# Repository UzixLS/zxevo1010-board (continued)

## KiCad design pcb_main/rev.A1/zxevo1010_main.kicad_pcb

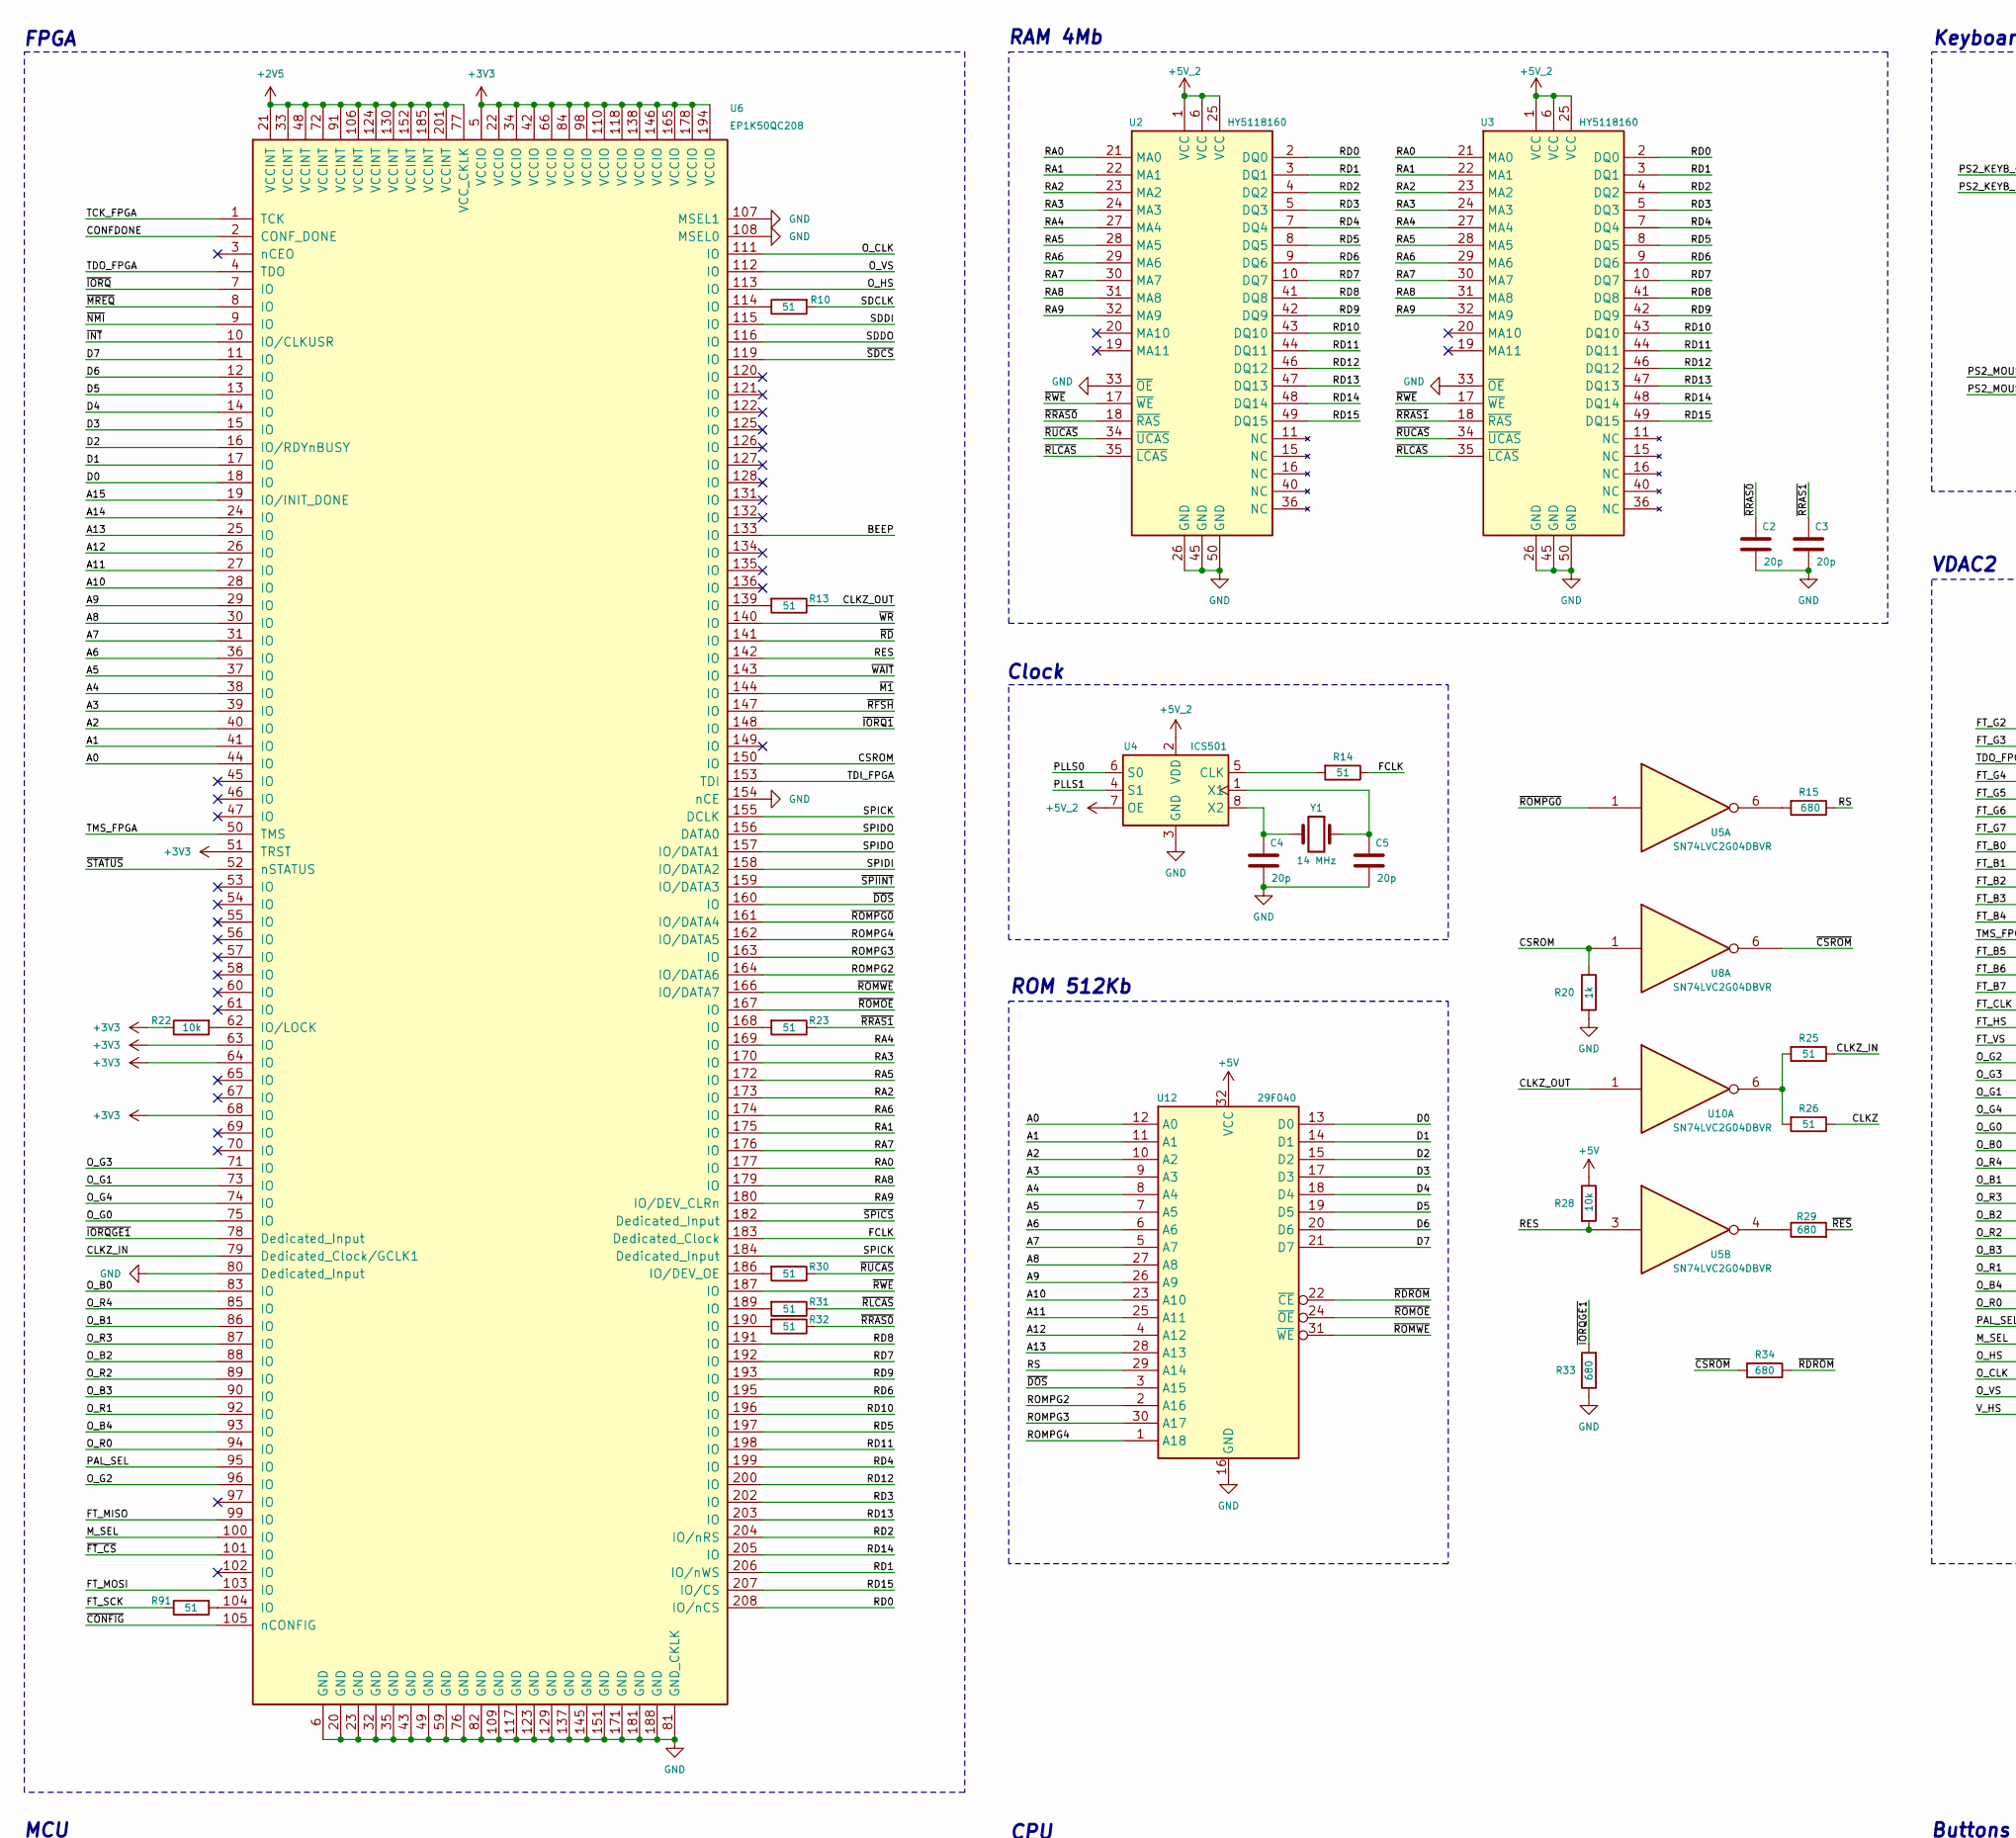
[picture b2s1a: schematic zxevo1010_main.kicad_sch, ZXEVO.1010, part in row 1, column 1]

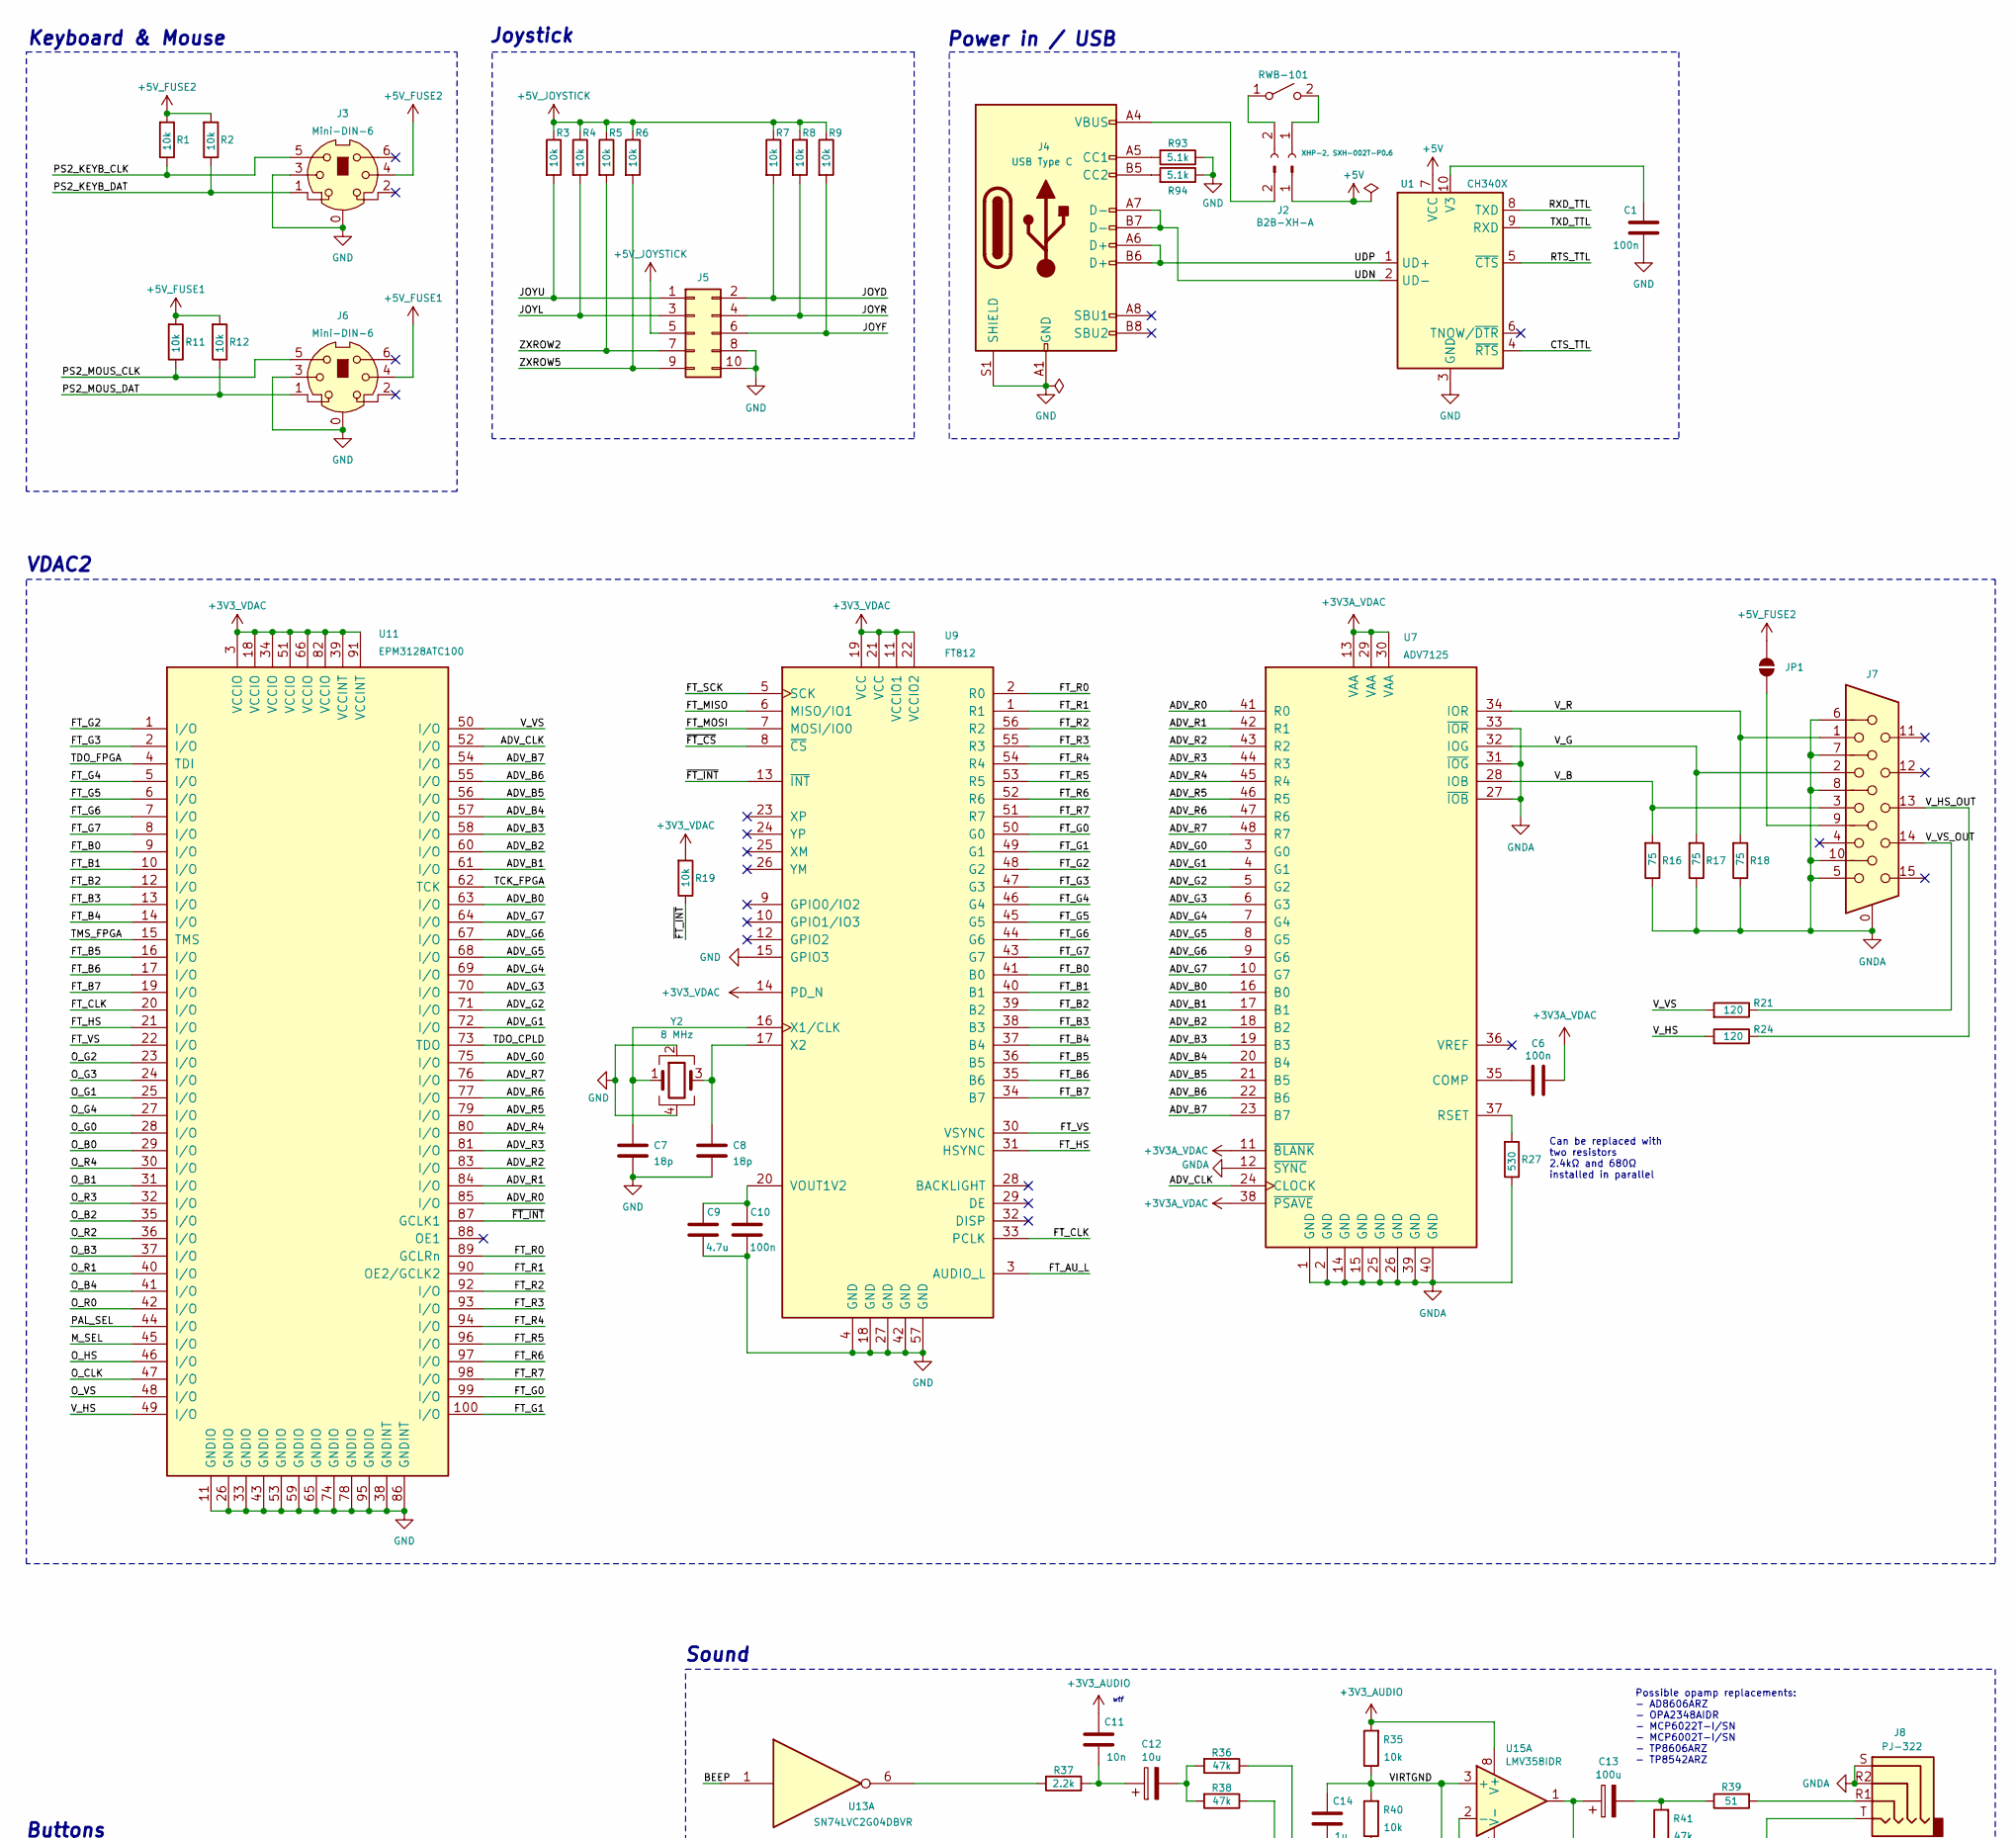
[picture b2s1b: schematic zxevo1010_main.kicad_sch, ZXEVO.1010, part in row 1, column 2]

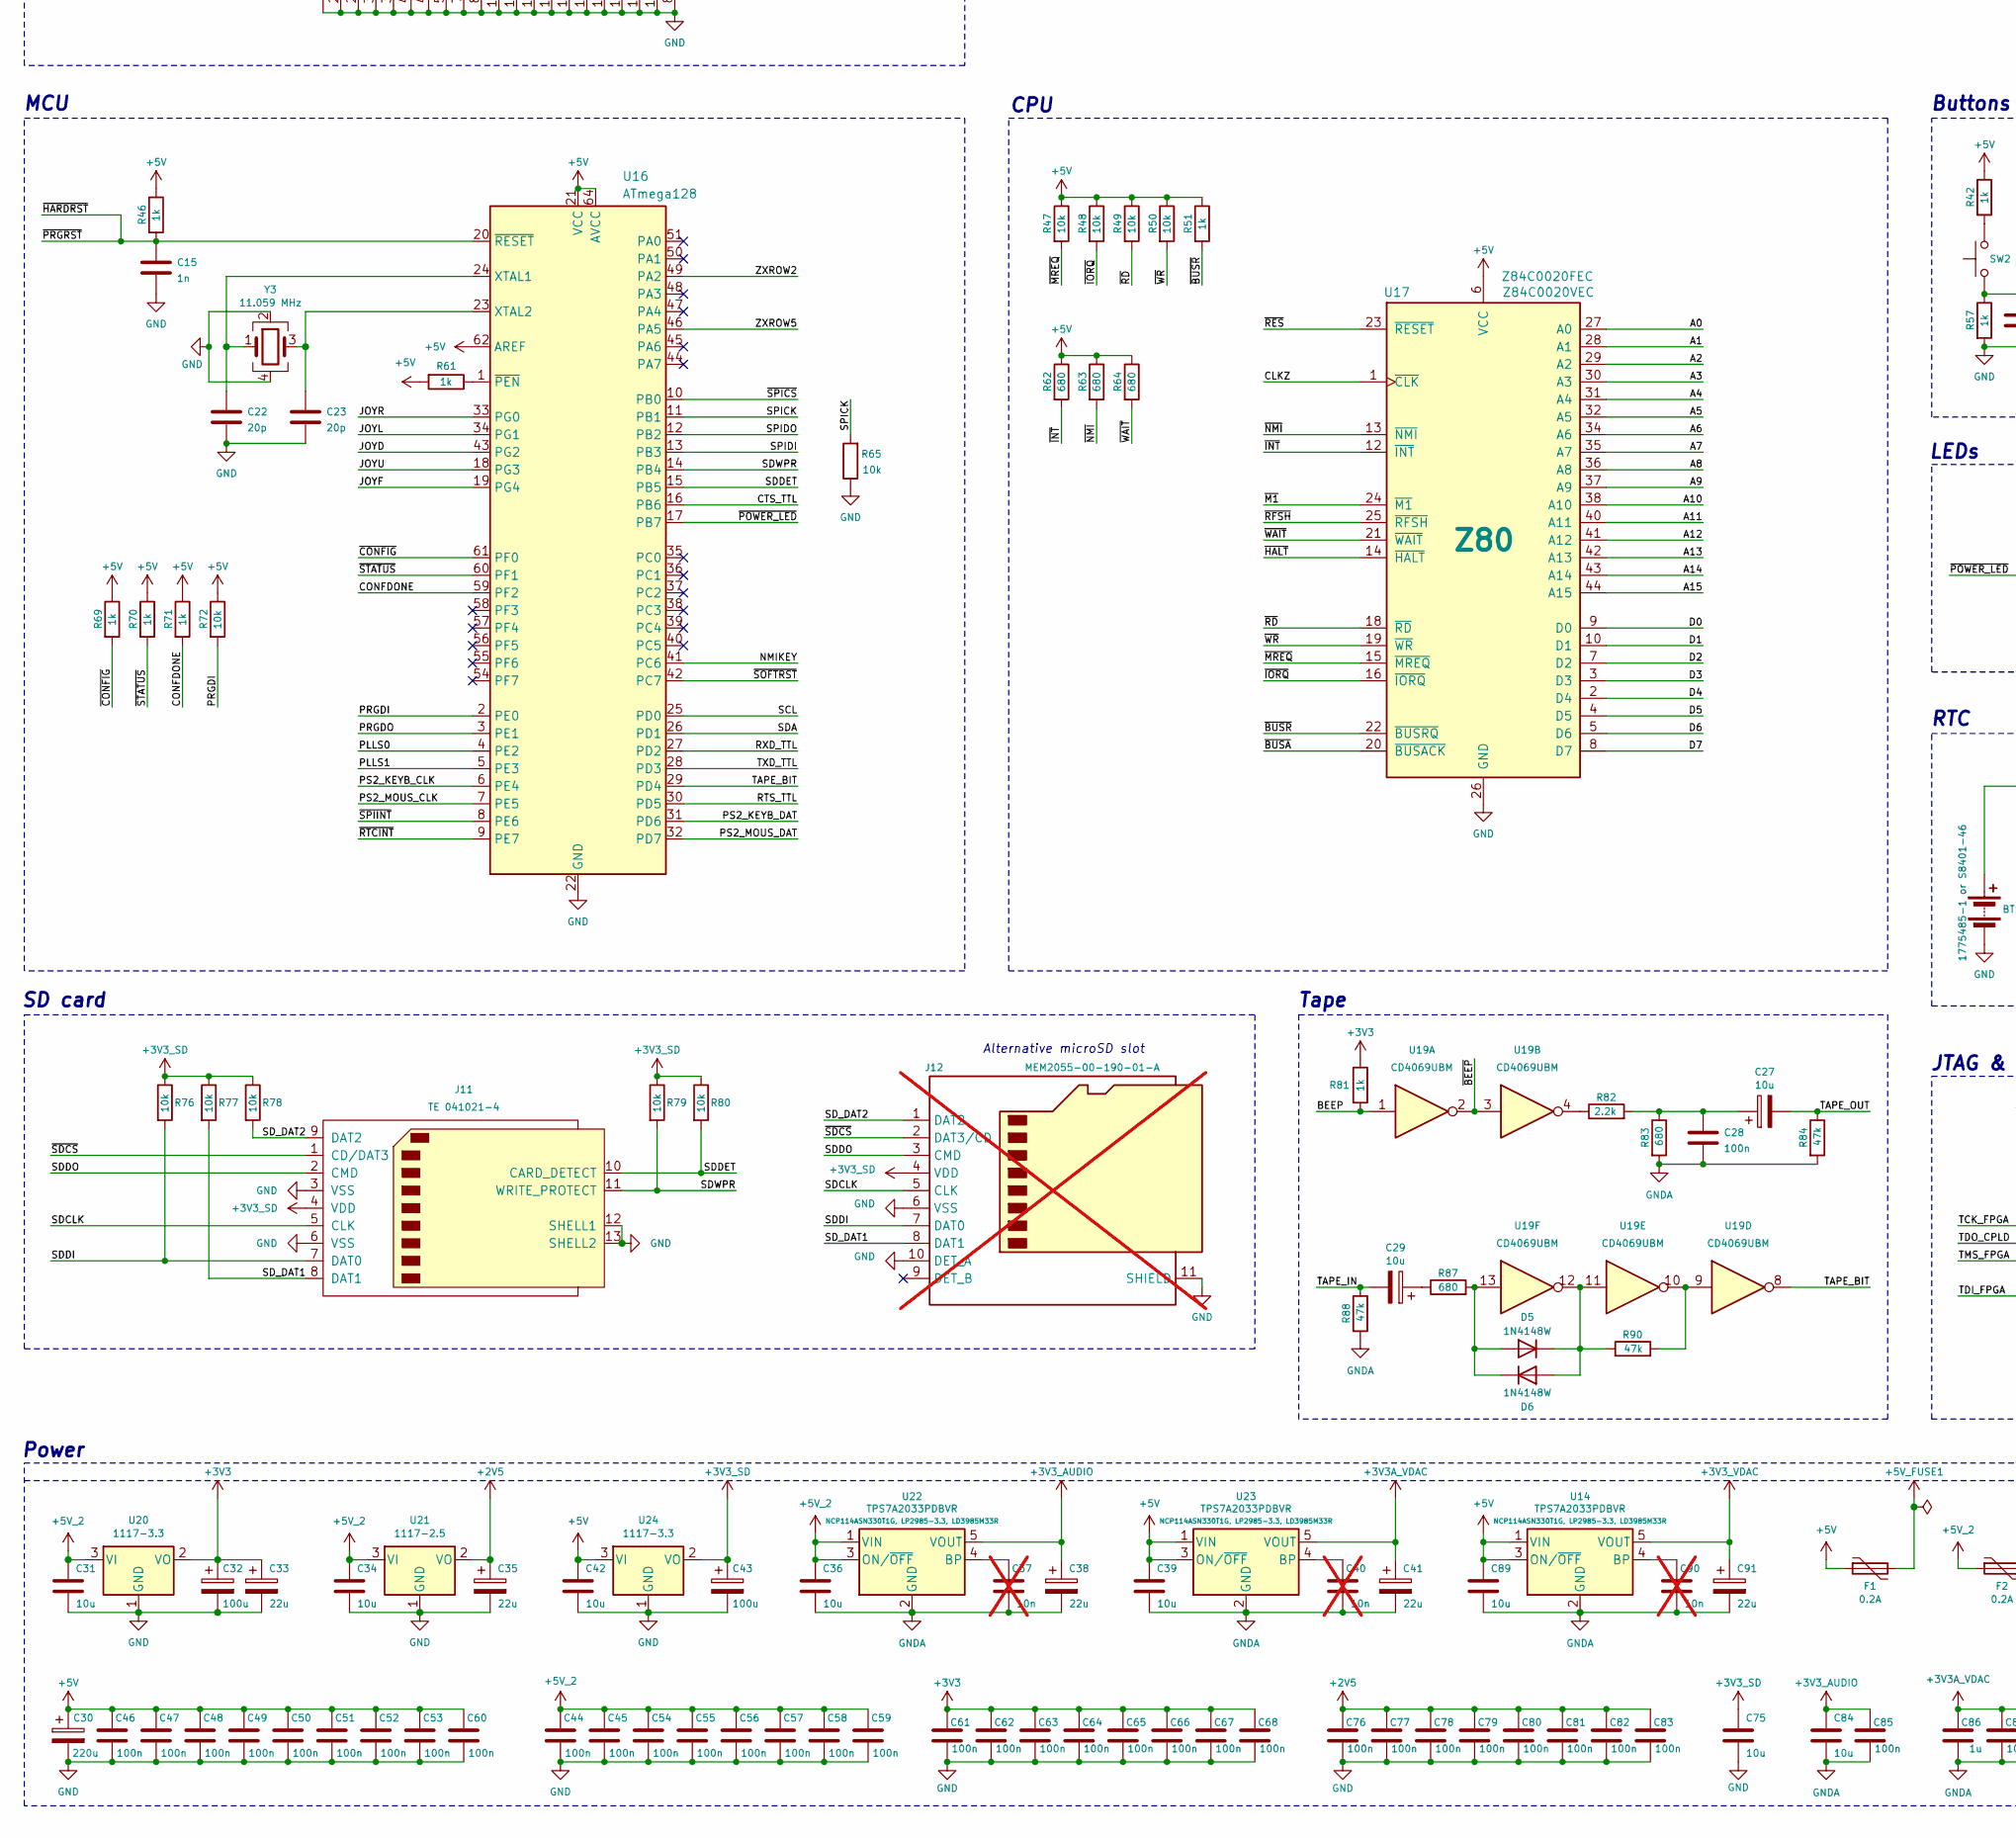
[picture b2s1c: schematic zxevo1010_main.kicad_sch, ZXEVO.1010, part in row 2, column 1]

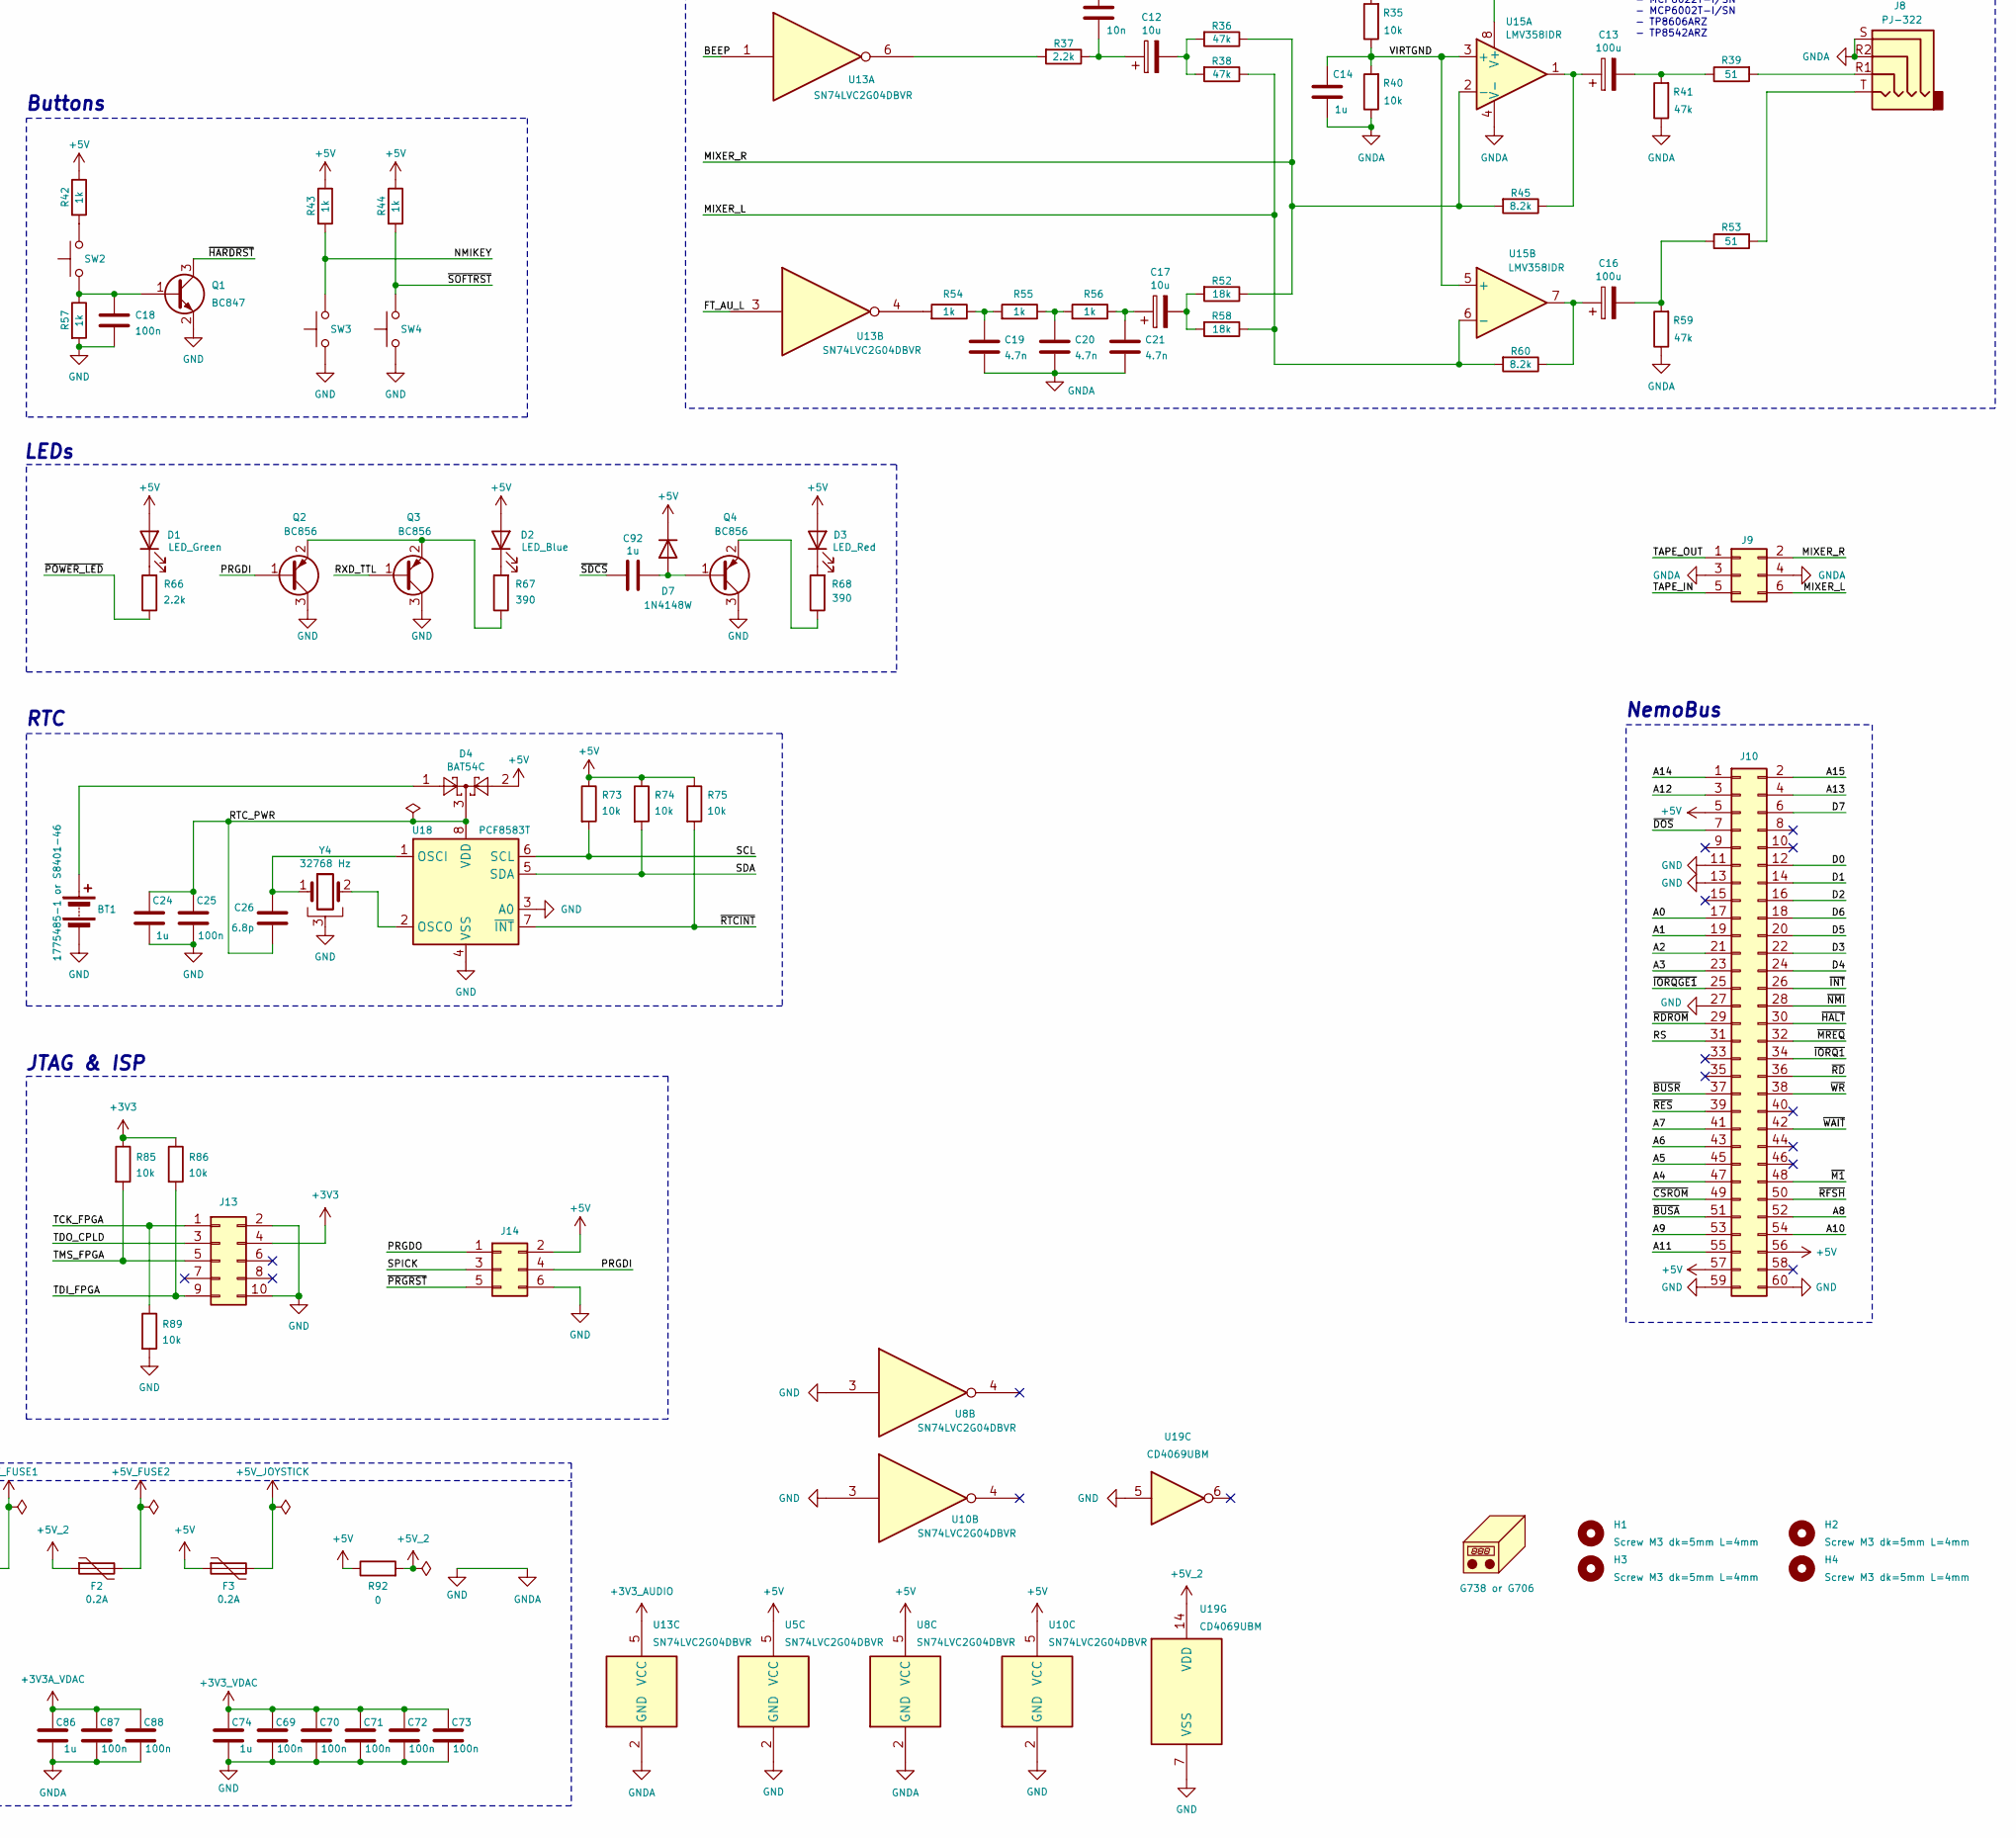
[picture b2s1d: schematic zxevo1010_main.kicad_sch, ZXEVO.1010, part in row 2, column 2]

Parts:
BT1: 1775485-1 or S8401-46; CR2032V
C1, C6, C10, C18, C25, C28, C44, C45, C46, C47, C48, C49, C50, C51, C52, C53, C54, C55, C56, C57, C58, C59, C60, C69, C70, C71, C72, C73, C85, C87, C88: 100n; C_0603_1608Metric_Pad1.08x0.95mm_HandSolder
C2, C3, C4, C5, C22, C23: 20p; C_0603_1608Metric_Pad1.08x0.95mm_HandSolder
C7, C8: 18p; C_0603_1608Metric_Pad1.08x0.95mm_HandSolder
C9: 4.7u; C_0603_1608Metric_Pad1.08x0.95mm_HandSolder
C11: 10n; C_0603_1608Metric_Pad1.08x0.95mm_HandSolder
C12, C17, C27, C29: 10u; CP_EIA-3216-18_Kemet-A_Pad1.58x1.35mm_HandSolder
C13, C16, C32, C43: 100u; CP_EIA-6032-28_Kemet-C_Pad2.25x2.35mm_HandSolder
C14, C24, C74, C86, C92: 1u; C_0603_1608Metric_Pad1.08x0.95mm_HandSolder
C15: 1n; C_0603_1608Metric_Pad1.08x0.95mm_HandSolder
C19, C20, C21: 4.7n; C_0603_1608Metric_Pad1.08x0.95mm_HandSolder
C26: 6.8p; C_0603_1608Metric_Pad1.08x0.95mm_HandSolder
C30: 220u; CP_Elec_6.3x7.7
C31, C34, C36, C39, C42, C75, C84, C89: 10u; C_0805_2012Metric_Pad1.18x1.45mm_HandSolder
C33, C35, C38, C41, C91: 22u; CP_EIA-3216-18_Kemet-A_Pad1.58x1.35mm_HandSolder
C37, C40, C90: 10n; C_0603_1608Metric_Pad1.08x0.95mm_HandSolder; not fitted
C61, C62, C63, C64, C65, C66, C67, C68, C76, C77, C78, C79, C80, C81, C82, C83: 100n; C_0805_2012Metric_Pad1.18x1.45mm_HandSolder
D1: LED_Green; LED_D5.0mm_Horizontal_O1.27mm_Z3.0mm
D2: LED_Blue; LED_D5.0mm_Horizontal_O1.27mm_Z3.0mm
D3: LED_Red; LED_D5.0mm_Horizontal_O1.27mm_Z3.0mm
D4: BAT54C; SOT-23
D5, D6, D7: 1N4148W; D_SOD-123
F1, F2, F3: 0.2A; Fuse_1812_4532Metric_Pad1.30x3.40mm_HandSolder
H1, H2, H3, H4: Screw M3 dk=5mm L=4mm; MountingHole_3.2mm_M3_dk5.2mm_Mask
J1: XHP-2, SXH-002T-P0.6
J2: B2B-XH-A; JST_XH_B2B-XH-A_1x02_P2.50mm_Vertical
J3, J6: Mini-DIN-6; minidin-6
J4: USB Type C; USB_C_Receptacle_HRO_TYPE-C-31-M-12_dangling
J5, J13: Conn_02x05_Odd_Even; PinHeader_2x05_P2.54mm_Vertical
J7: DB15_Female_HighDensity_MountingHoles; DSUB-15-HD_Female_Horizontal_P2.29x1.98mm_EdgePinOffset3.03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
J8: PJ-322
J9, J14: Conn_02x05_Odd_Even; PinHeader_2x03_P2.54mm_Vertical
J10: Conn_02x30_Row_Letter_First; PinSocket_2x30_P2.54mm_Vertical
J11: TE 041021-4; SD_TE_2041021-mod
J12: MEM2055-00-190-01-A; GCT-MEM2055-00-190-01-A; not fitted
JP1: SolderJumper_2_Open; SolderJumper-2_P1.3mm_Open_RoundedPad1.0x1.5mm
N1: G738 or G706; g738-g706
Q1: BC847; SOT-23
Q2, Q3, Q4: BC856; SOT-23
R1, R2, R3, R4, R5, R6, R7, R8, R9, R11, R12, R19, R22, R28, R35, R40, R47, R48, R49, R50, R65, R72, R73, R74, R75, R76, R77, R78, R79, R80, R85, R86, R89: 10k; R_0603_1608Metric_Pad0.98x0.95mm_HandSolder
R10, R13, R14, R23, R25, R26, R30, R31, R32, R39, R53, R91: 51; R_0603_1608Metric_Pad0.98x0.95mm_HandSolder
R15, R29, R33, R34, R62, R63, R64, R83, R87: 680; R_0603_1608Metric_Pad0.98x0.95mm_HandSolder
R16, R17, R18: 75; R_0603_1608Metric_Pad0.98x0.95mm_HandSolder
R20, R42, R43, R44, R46, R51, R54, R55, R56, R57, R61, R69, R70, R71, R81: 1k; R_0603_1608Metric_Pad0.98x0.95mm_HandSolder
R21, R24: 120; R_0603_1608Metric_Pad0.98x0.95mm_HandSolder
R27: 530; R_0603_1608Metric_Pad0.98x0.95mm_HandSolder
R36, R38, R41, R59, R84, R88, R90: 47k; R_0603_1608Metric_Pad0.98x0.95mm_HandSolder
R37, R66, R82: 2.2k; R_0603_1608Metric_Pad0.98x0.95mm_HandSolder
R45, R60: 8.2k; R_0603_1608Metric_Pad0.98x0.95mm_HandSolder
R52, R58: 18k; R_0603_1608Metric_Pad0.98x0.95mm_HandSolder
R67, R68: 390; R_0603_1608Metric_Pad0.98x0.95mm_HandSolder
R92: 0; R_1206_3216Metric
R93, R94: 5.1k; R_0603_1608Metric_Pad0.98x0.95mm_HandSolder
SW1: RWB-101
SW2, SW3, SW4: Push angle button, 6x6x7mm or 6x6x8mm; SW_Tactile_SPST_Angled_PTS645Vx58-2LFS
U1: CH340X; MSOP-10_3x3mm_P0.5mm
U2, U3: HY5118160; TSOP-II-44-50_P0.8mm
U4: ICS501; SOIC-8_3.9x4.9mm_P1.27mm
U5, U8, U10, U13: SN74LVC2G04DBVR; SOT-23-6_Handsoldering
U6: EP1K50QC208; PQFP-208_28x28mm_P0.5mm_LongPads
U7: ADV7125; TQFP-48_7x7mm_P0.5mm
U9: FT812; QFN-56-1EP_8x8mm_P0.5mm_EP4.3x4.3mm
U11: EPM3128ATC100; TQFP-100_14x14mm_P0.5mm
U12: 29F040; PLCC-32_11.4x14.0mm_P1.27mm-longpads
U14, U22, U23: TPS7A2033PDBVR; SOT-23-5_HandSoldering
U15: LMV358IDR; SOIC-8_3.9x4.9mm_P1.27mm
U16: ATmega128; TQFP-64_14x14mm_P0.8mm
U17: Z84C0020FEC; Z80_FEC_VEC
U18: PCF8583T; SOT176-1
U19: CD4069UBM; SO-14_3.9x8.65mm_P1.27mm
U20, U24: 1117-3.3; SOT-223-3_TabPin2
U21: 1117-2.5; SOT-223-3_TabPin2
Y1: 14 MHz; Crystal_HC49-4H_Vertical
Y2: 8 MHz; Crystal_SMD_3225-4Pin_3.2x2.5mm_HandSoldering
Y3: 11.059 MHz; Crystal_SMD_3225-4Pin_3.2x2.5mm_HandSoldering
Y4: 32768 Hz; Crystal_C38-LF_D3.0mm_L8.0mm_Horizontal_1EP_style2

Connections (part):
+2V5: C35.1, C76.1, C77.1, C78.1, C79.1, C80.1, C81.1, C82.1, C83.1, U6.21 (VCCINT), U6.33 (VCCINT), U6.48 (VCCINT), U6.72 (VCCINT), U6.77 (VCC_CKLK), U6.91 (VCCINT), U6.106 (VCCINT), U6.124 (VCCINT), U6.130 (VCCINT), U6.152 (VCCINT), U6.185 (VCCINT), U6.201 (VCCINT), U21.2 (VO)
+3V3: C32.1, C33.1, C61.1, C62.1, C63.1, C64.1, C65.1, C66.1, C67.1, C68.1, J13.4, R22.1, R81.1, R85.1, R86.1, U6.5 (VCCIO), U6.22 (VCCIO), U6.34 (VCCIO), U6.42 (VCCIO), U6.51 (TRST), U6.63 (IO), U6.64 (IO), U6.66 (VCCIO), U6.68 (IO), U6.84 (VCCIO), U6.98 (VCCIO), U6.110 (VCCIO), U6.118 (VCCIO), U6.138 (VCCIO), U6.146 (VCCIO), U6.165 (VCCIO), U6.178 (VCCIO), U6.194 (VCCIO), U20.2 (VO)
+3V3A_VDAC: C6.1, C41.1, C86.1, C87.1, C88.1, U7.11 (~BLANK), U7.13 (VAA), U7.29 (VAA), U7.30 (VAA), U7.38 (~PSAVE), U23.5 (VOUT)
+3V3_AUDIO: C11.2, C38.1, C84.2, C85.1, R35.2, U13.5 (VCC), U15.8 (V+), U22.5 (VOUT)
+3V3_SD: C43.1, C75.2, J11.4 (VDD), J12.4 (VDD), R76.1, R77.1, R78.1, R79.1, R80.1, U24.2 (VO)
+3V3_VDAC: C69.1, C70.1, C71.1, C72.1, C73.1, C74.1, C91.1, R19.2, U9.11 (VCCIO1), U9.14 (PD_N), U9.19 (VCC), U9.21 (VCC), U9.22 (VCCIO2), U11.3 (VCCIO), U11.18 (VCCIO), U11.34 (VCCIO), U11.39 (VCCINT), U11.51 (VCCIO), U11.66 (VCCIO), U11.82 (VCCIO), U11.91 (VCCINT), U14.5 (VOUT)
+5V: C30.1, C39.2, C42.2, C46.2, C47.2, C48.2, C49.2, C50.2, C51.2, C52.2, C53.2, C60.2, C89.2, D1.2 (A), D2.2 (A), D3.2 (A), D4.2, D7.1 (K), F1.1, F3.1, J2.1, J10.5, J10.56, J10.57, J14.2, R28.1, R42.1, R43.1, R44.1, R46.1, R47.1, R48.1, R49.1, R50.1, R51.1, R61.2, R62.1, R63.1, R64.1, R69.1, R70.1, R71.1, R72.1, R73.1, R74.1, R75.1, R92.1, U1.7 (VCC), U5.5 (VCC), U8.5 (VCC), U10.5 (VCC), U12.32 (VCC), U14.1 (VIN), U14.3 (ON/~OFF), U16.21 (VCC), U16.52 (VCC), U16.62 (AREF), U16.64 (AVCC), U17.6 (VCC), U23.1 (VIN), U23.3 (ON/~OFF), U24.3 (VI)
+5V_2: C31.2, C34.2, C36.2, C44.2, C45.2, C54.2, C55.2, C56.2, C57.2, C58.2, C59.2, F2.1, R92.2, U2.1 (VCC), U2.6 (VCC), U2.25 (VCC), U3.1 (VCC), U3.6 (VCC), U3.25 (VCC), U4.2 (VDD), U4.7 (OE), U19.14 (VDD), U20.3 (VI), U21.3 (VI), U22.1 (VIN), U22.3 (ON/~OFF)
+5V_FUSE1: F1.2, J6.4, R11.2, R12.2
+5V_FUSE2: F2.2, J3.4, JP1.2 (B), R1.2, R2.2
+5V_JOYSTICK: F3.2, J5.5, R3.1, R4.1, R5.1, R6.1, R7.1, R8.1, R9.1
/A0: J10.17, U6.44 (IO), U12.12 (A0), U17.27 (A0)
/A1: J10.19, U6.41 (IO), U12.11 (A1), U17.28 (A1)
/A2: J10.21, U6.40 (IO), U12.10 (A2), U17.29 (A2)
/A3: J10.23, U6.39 (IO), U12.9 (A3), U17.30 (A3)
/A4: J10.47, U6.38 (IO), U12.8 (A4), U17.31 (A4)
/A5: J10.45, U6.37 (IO), U12.7 (A5), U17.32 (A5)
/A6: J10.43, U6.36 (IO), U12.6 (A6), U17.34 (A6)
/A7: J10.41, U6.31 (IO), U12.5 (A7), U17.35 (A7)
/A8: J10.52, U6.30 (IO), U12.27 (A8), U17.36 (A8)
/A9: J10.53, U6.29 (IO), U12.26 (A9), U17.37 (A9)
/A10: J10.54, U6.28 (IO), U12.23 (A10), U17.38 (A10)
/A11: J10.55, U6.27 (IO), U12.25 (A11), U17.40 (A11)
/A12: J10.3, U6.26 (IO), U12.4 (A12), U17.41 (A12)
/A13: J10.4, U6.25 (IO), U12.28 (A13), U17.42 (A13)
/A14: J10.1, U6.24 (IO), U17.43 (A14)
/A15: J10.2, U6.19 (IO/INIT_DONE), U17.44 (A15)
/ADV_B0: U7.16 (B0), U11.63 (I/O)
/ADV_B1: U7.17 (B1), U11.61 (I/O)
/ADV_B2: U7.18 (B2), U11.60 (I/O)
/ADV_B3: U7.19 (B3), U11.58 (I/O)
/ADV_B4: U7.20 (B4), U11.57 (I/O)
/ADV_B5: U7.21 (B5), U11.56 (I/O)
/ADV_B6: U7.22 (B6), U11.55 (I/O)
/ADV_B7: U7.23 (B7), U11.54 (I/O)
/ADV_CLK: U7.24 (CLOCK), U11.52 (I/O)
/ADV_G0: U7.3 (G0), U11.75 (I/O)
/ADV_G1: U7.4 (G1), U11.72 (I/O)
/ADV_G2: U7.5 (G2), U11.71 (I/O)
/ADV_G3: U7.6 (G3), U11.70 (I/O)
/ADV_G4: U7.7 (G4), U11.69 (I/O)
/ADV_G5: U7.8 (G5), U11.68 (I/O)
/ADV_G6: U7.9 (G6), U11.67 (I/O)
/ADV_G7: U7.10 (G7), U11.64 (I/O)
/ADV_R0: U7.41 (R0), U11.85 (I/O)
/ADV_R1: U7.42 (R1), U11.84 (I/O)
/ADV_R2: U7.43 (R2), U11.83 (I/O)
/ADV_R3: U7.44 (R3), U11.81 (I/O)
/ADV_R4: U7.45 (R4), U11.80 (I/O)
/ADV_R5: U7.46 (R5), U11.79 (I/O)
/ADV_R6: U7.47 (R6), U11.77 (I/O)
/ADV_R7: U7.48 (R7), U11.76 (I/O)
/BEEP: R81.2, U6.133 (IO), U13.1, U19.1
/CLKZ: R26.1, U17.1 (~CLK)
/CLKZ_IN: R25.1, U6.79 (Dedicated_Clock/GCLK1)
/CLKZ_OUT: R13.1, U10.1
/CONFDONE: R71.2, U6.2 (CONF_DONE), U16.59 (PF2)
/CSROM: R20.1, U6.150 (IO), U8.1
/CTS_TTL: U1.4 (~RTS), U16.16 (PB6)
/D0: J10.12, U6.18 (IO), U12.13 (D0), U17.9 (D0)
/D1: J10.14, U6.17 (IO), U12.14 (D1), U17.10 (D1)
/D2: J10.16, U6.16 (IO/RDYnBUSY), U12.15 (D2), U17.7 (D2)
/D3: J10.22, U6.15 (IO), U12.17 (D3), U17.3 (D3)
/D4: J10.24, U6.14 (IO), U12.18 (D4), U17.2 (D4)
/D5: J10.20, U6.13 (IO), U12.19 (D5), U17.4 (D5)
/D6: J10.18, U6.12 (IO), U12.20 (D6), U17.5 (D6)
/D7: J10.6, U6.11 (IO), U12.21 (D7), U17.8 (D7)
/FCLK: R14.1, U6.183 (Dedicated_Clock)
/FT_AU_L: U9.3 (AUDIO_L), U13.3
/FT_B0: U9.41 (B0), U11.9 (I/O)
/FT_B1: U9.40 (B1), U11.10 (I/O)
/FT_B2: U9.39 (B2), U11.12 (I/O)
/FT_B3: U9.38 (B3), U11.13 (I/O)
/FT_B4: U9.37 (B4), U11.14 (I/O)
/FT_B5: U9.36 (B5), U11.16 (I/O)
/FT_B6: U9.35 (B6), U11.17 (I/O)
/FT_B7: U9.34 (B7), U11.19 (I/O)
/FT_CLK: U9.33 (PCLK), U11.20 (I/O)
/FT_G0: U9.50 (G0), U11.99 (I/O)
/FT_G1: U9.49 (G1), U11.100 (I/O)
/FT_G2: U9.48 (G2), U11.1 (I/O)
/FT_G3: U9.47 (G3), U11.2 (I/O)
/FT_G4: U9.46 (G4), U11.5 (I/O)
/FT_G5: U9.45 (G5), U11.6 (I/O)
/FT_G6: U9.44 (G6), U11.7 (I/O)
/FT_G7: U9.43 (G7), U11.8 (I/O)
/FT_HS: U9.31 (HSYNC), U11.21 (I/O)
/FT_MISO: U6.99 (IO), U9.6 (MISO/IO1)
/FT_MOSI: U6.103 (IO), U9.7 (MOSI/IO0)
/FT_R0: U9.2 (R0), U11.89 (GCLRn)
/FT_R1: U9.1 (R1), U11.90 (OE2/GCLK2)
/FT_R2: U9.56 (R2), U11.92 (I/O)
/FT_R3: U9.55 (R3), U11.93 (I/O)
/FT_R4: U9.54 (R4), U11.94 (I/O)
/FT_R5: U9.53 (R5), U11.96 (I/O)
/FT_R6: U9.52 (R6), U11.97 (I/O)
/FT_R7: U9.51 (R7), U11.98 (I/O)
/FT_SCK: R91.1, U9.5 (SCK)
/FT_VS: U9.30 (VSYNC), U11.22 (I/O)
/JOYD: J5.2, R7.2, U16.43 (PG2)
/JOYF: J5.6, R9.2, U16.19 (PG4)
/JOYL: J5.3, R4.2, U16.34 (PG1)
/JOYR: J5.4, R8.2, U16.33 (PG0)
/JOYU: J5.1, R3.2, U16.18 (PG3)
/MIXER_L: J9.6, R38.1, R58.1, R60.2, U15.6 (-)
/MIXER_R: J9.2, R36.1, R45.2, R52.1, U15.2 (-)
/M_SEL: U6.100 (IO), U11.45 (I/O)
/NMIKEY: R43.2, SW3.1, U16.41 (PC6)
/O_B0: U6.83 (IO), U11.29 (I/O)
/O_B1: U6.86 (IO), U11.31 (I/O)
/O_B2: U6.88 (IO), U11.35 (I/O)
/O_B3: U6.90 (IO), U11.37 (I/O)
/O_B4: U6.93 (IO), U11.41 (I/O)
/O_CLK: U6.111 (IO), U11.47 (I/O)
/O_G0: U6.75 (IO), U11.28 (I/O)
/O_G1: U6.73 (IO), U11.25 (I/O)
/O_G2: U6.96 (IO), U11.23 (I/O)
/O_G3: U6.71 (IO), U11.24 (I/O)
/O_G4: U6.74 (IO), U11.27 (I/O)
/O_HS: U6.113 (IO), U11.46 (I/O)
/O_R0: U6.94 (IO), U11.42 (I/O)
/O_R1: U6.92 (IO), U11.40 (I/O)
/O_R2: U6.89 (IO), U11.36 (I/O)
/O_R3: U6.87 (IO), U11.32 (I/O)
/O_R4: U6.85 (IO), U11.30 (I/O)
/O_VS: U6.112 (IO), U11.48 (I/O)
/PAL_SEL: U6.95 (IO), U11.44 (I/O)
/PLLS0: U4.6 (S0), U16.4 (PE2)
/PLLS1: U4.4 (S1), U16.5 (PE3)
/PRGDI: J14.4, Q2.1 (B), R72.2, U16.2 (PE0)
/PRGDO: J14.1, U16.3 (PE1)
/PS2_KEYB_CLK: J3.5, R1.1, U16.6 (PE4)
/PS2_KEYB_DAT: J3.1, R2.1, U16.31 (PD6)
/PS2_MOUS_CLK: J6.5, R11.1, U16.7 (PE5)
/PS2_MOUS_DAT: J6.1, R12.1, U16.32 (PD7)
/RA0: U2.21 (MA0), U3.21 (MA0), U6.177 (IO)
/RA1: U2.22 (MA1), U3.22 (MA1), U6.175 (IO)
/RA2: U2.23 (MA2), U3.23 (MA2), U6.173 (IO)
/RA3: U2.24 (MA3), U3.24 (MA3), U6.170 (IO)
/RA4: U2.27 (MA4), U3.27 (MA4), U6.169 (IO)
/RA5: U2.28 (MA5), U3.28 (MA5), U6.172 (IO)
/RA6: U2.29 (MA6), U3.29 (MA6), U6.174 (IO)
/RA7: U2.30 (MA7), U3.30 (MA7), U6.176 (IO)
/RA8: U2.31 (MA8), U3.31 (MA8), U6.179 (IO)
/RA9: U2.32 (MA9), U3.32 (MA9), U6.180 (IO/DEV_CLRn)
/RD0: U2.2 (DQ0), U3.2 (DQ0), U6.208 (IO/nCS)
/RD1: U2.3 (DQ1), U3.3 (DQ1), U6.206 (IO/nWS)
/RD2: U2.4 (DQ2), U3.4 (DQ2), U6.204 (IO/nRS)
/RD3: U2.5 (DQ3), U3.5 (DQ3), U6.202 (IO)
/RD4: U2.7 (DQ4), U3.7 (DQ4), U6.199 (IO)
/RD5: U2.8 (DQ5), U3.8 (DQ5), U6.197 (IO)
/RD6: U2.9 (DQ6), U3.9 (DQ6), U6.195 (IO)
/RD7: U2.10 (DQ7), U3.10 (DQ7), U6.192 (IO)
/RD8: U2.41 (DQ8), U3.41 (DQ8), U6.191 (IO)
/RD9: U2.42 (DQ9), U3.42 (DQ9), U6.193 (IO)
/RD10: U2.43 (DQ10), U3.43 (DQ10), U6.196 (IO)
/RD11: U2.44 (DQ11), U3.44 (DQ11), U6.198 (IO)
/RD12: U2.46 (DQ12), U3.46 (DQ12), U6.200 (IO)
/RD13: U2.47 (DQ13), U3.47 (DQ13), U6.203 (IO)
/RD14: U2.48 (DQ14), U3.48 (DQ14), U6.205 (IO)
/RD15: U2.49 (DQ15), U3.49 (DQ15), U6.207 (IO/CS)
/RES: R28.2, U5.3, U6.142 (IO)
/ROMPG2: U6.164 (IO/DATA6), U12.2 (A16)
/ROMPG3: U6.163 (IO), U12.30 (A17)
/ROMPG4: U6.162 (IO/DATA5), U12.1 (A18)
/RS: J10.31, R15.1, U12.29 (A14)
/RTC_PWR: C24.2, C25.2, C26.2, D4.3, U18.8 (VDD)
/RTS_TTL: U1.5 (~CTS), U16.30 (PD5)
/RXD_TTL: Q3.1 (B), U1.8 (TXD), U16.27 (PD2)
/SCL: R73.2, U16.25 (PD0), U18.6 (SCL)
/SDA: R74.2, U16.26 (PD1), U18.5 (SDA)
/SDCLK: J11.5 (CLK), J12.5 (CLK), R10.2
/SDDET: J11.10 (CARD_DETECT), R80.2, U16.15 (PB5)
/SDDI: J11.7 (DAT0), J12.7 (DAT0), R76.2, U6.115 (IO)
/SDDO: J11.2 (CMD), J12.3 (CMD), U6.116 (IO)
/SDWPR: J11.11 (WRITE_PROTECT), R79.2, U16.14 (PB4)
/SD_DAT1: J11.8 (DAT1), J12.8 (DAT1), R77.2
/SD_DAT2: J11.9 (DAT2), J12.1 (DAT2), R78.2
/SPICK: J14.3, R65.2, U6.155 (DCLK), U6.184 (Dedicated_Input), U16.11 (PB1)
/SPIDI: U6.158 (IO/DATA2), U16.13 (PB3)
/SPIDO: U6.156 (DATA0), U6.157 (IO/DATA1), U16.12 (PB2)
/TAPE_BIT: U16.29 (PD4), U19.8
/TAPE_IN: C29.2, J9.5, R88.1
/TAPE_OUT: C27.2, J9.1, R84.1
/TCK_FPGA: J13.1, R89.1, U6.1 (TCK), U11.62 (TCK)
/TDI_FPGA: J13.9, R86.2, U6.153 (TDI)
/TDO_CPLD: J13.3, U11.73 (TDO)
/TDO_FPGA: U6.4 (TDO), U11.4 (TDI)
/TMS_FPGA: J13.5, R85.2, U6.50 (TMS), U11.15 (TMS)
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
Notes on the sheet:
CPU
VDAC2
wtf
Can be replaced with two resistors 2.4kΩ and 680Ω installed in parallel
RAM 4Mb
Keyboard & Mouse
JTAG & ISP
Buttons
LEDs
NemoBus
RTC
SD card
ROM 512Kb
Possible opamp replacements: - AD8606ARZ - OPA2348AIDR - MCP6022T-I/SN - MCP6002T-I/SN - TP8606ARZ - TP8542ARZ
Clock
Tape
MCU
Sound
Joystick
Power in / USB
Alternative microSD slot
Power
FPGA
